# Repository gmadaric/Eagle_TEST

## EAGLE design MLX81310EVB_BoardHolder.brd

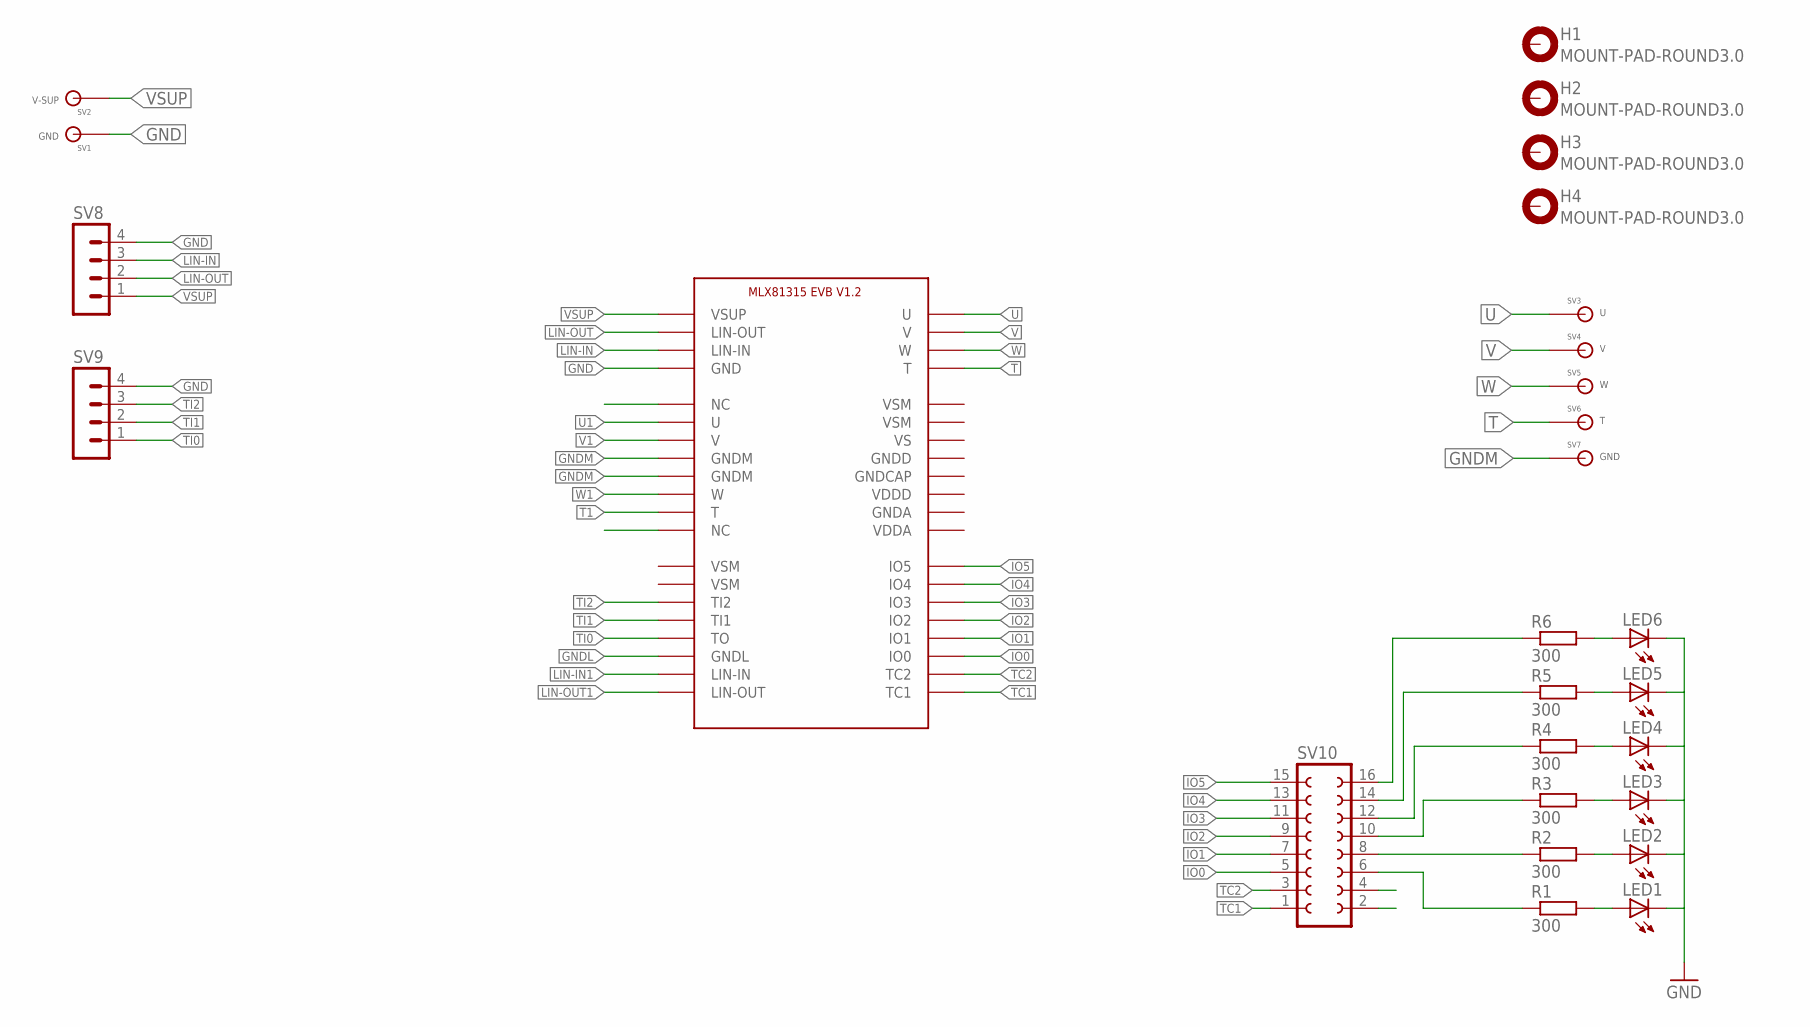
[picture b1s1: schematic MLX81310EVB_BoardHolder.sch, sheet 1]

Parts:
B1: MLX91315_EVB; MLX81315EVB
H1, H2, H3, H4: MOUNT-PAD-ROUND3.0; 3,0-PAD
LED1, LED2, LED3, LED4, LED5, LED6: LEDCHIPLED_0805; CHIPLED_0805; DIGI-KEY 160-1218-1-ND
R1, R2, R3, R4, R5, R6: 300; M0805; DIGI-KEY RR12P300DCT-ND
SV1, SV7: GND; BANANNA_CONNECTOR_SOLIDER_4MM
SV2: V-SUP; BANANNA_CONNECTOR_SOLIDER_4MM
SV3: U; BANANNA_CONNECTOR_SOLIDER_4MM
SV4: V; BANANNA_CONNECTOR_SOLIDER_4MM
SV5: W; BANANNA_CONNECTOR_SOLIDER_4MM
SV6: T; BANANNA_CONNECTOR_SOLIDER_4MM
SV8, SV9: MA04-1; DIGI-KEY 732-5317-ND
SV10: FE08-2; DIGI-KEY 609-3364-ND

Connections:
GND: B1.GND@1 (GND), LED1.C, LED2.C, LED3.C, LED4.C, LED5.C, LED6.C, SV1.P$1, SV8.4, SV9.4
GNDL: B1.GNDL
GNDM: B1.GNDM@1 (GNDM), B1.GNDM@2 (GNDM), SV7.P$1
IO0: B1.IO0, SV10.5
IO1: B1.IO1, SV10.7
IO2: B1.IO2, SV10.9
IO3: B1.IO3, SV10.11
IO4: B1.IO4, SV10.13
IO5: B1.IO5, SV10.15
LIN-IN: B1.LIN-IN@1 (LIN-IN), SV8.3
LIN-IN1: B1.LIN-IN@2 (LIN-IN)
LIN-OUT: B1.LIN-OUT@1 (LIN-OUT), SV8.2
LIN-OUT1: B1.LIN-OUT@2 (LIN-OUT)
unnamed: R6.1, SV10.16
unnamed: R4.1, SV10.12
unnamed: R1.1, SV10.6
unnamed: R2.1, SV10.8
unnamed: LED1.A, R1.2
unnamed: R3.1, SV10.10
unnamed: R5.1, SV10.14
unnamed: LED6.A, R6.2
unnamed: LED5.A, R5.2
unnamed: LED4.A, R4.2
unnamed: LED3.A, R3.2
unnamed: LED2.A, R2.2
T: B1.T@1 (T), SV6.P$1
T1: B1.T@2 (T)
TC1: B1.TC1, SV10.1, SV10.2
TC2: B1.TC2, SV10.3, SV10.4
TI0: B1.T0 (TO), SV9.1
TI1: B1.TI1, SV9.2
TI2: B1.TI2, SV9.3
U: B1.U@1 (U), SV3.P$1
U1: B1.U@2 (U)
V: B1.V@1 (V), SV4.P$1
V1: B1.V@2 (V)
VSUP: B1.VSUP, SV2.P$1, SV8.1
W: B1.W@1 (W), SV5.P$1
W1: B1.W@2 (W)

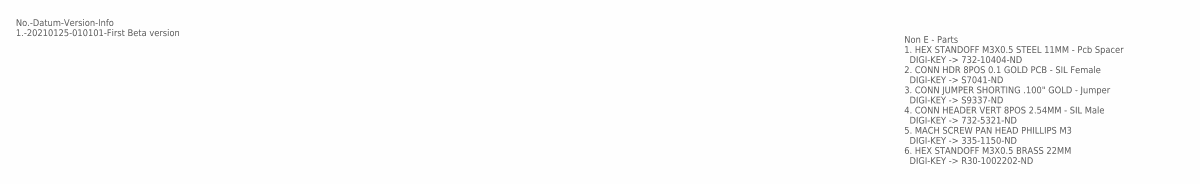
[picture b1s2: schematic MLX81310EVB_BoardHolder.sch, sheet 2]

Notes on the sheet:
No.-Datum-Version-Info 1.-20210125-010101-First Beta version
Non E - Parts 1. HEX STANDOFF M3X0.5 STEEL 11MM - Pcb Spacer DIGI-KEY -> 732-10404-ND 2. CONN HDR 8POS 0.1 GOLD PCB - SIL Female DIGI-KEY -> S7041-ND 3. CONN JUMPER SHORTING .100" GOLD - Jumper DIGI-KEY -> S9337-ND 4. CONN HEADER VERT 8POS 2.54MM - SIL Male DIGI-KEY -> 732-5321-ND 5. MACH SCREW PAN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

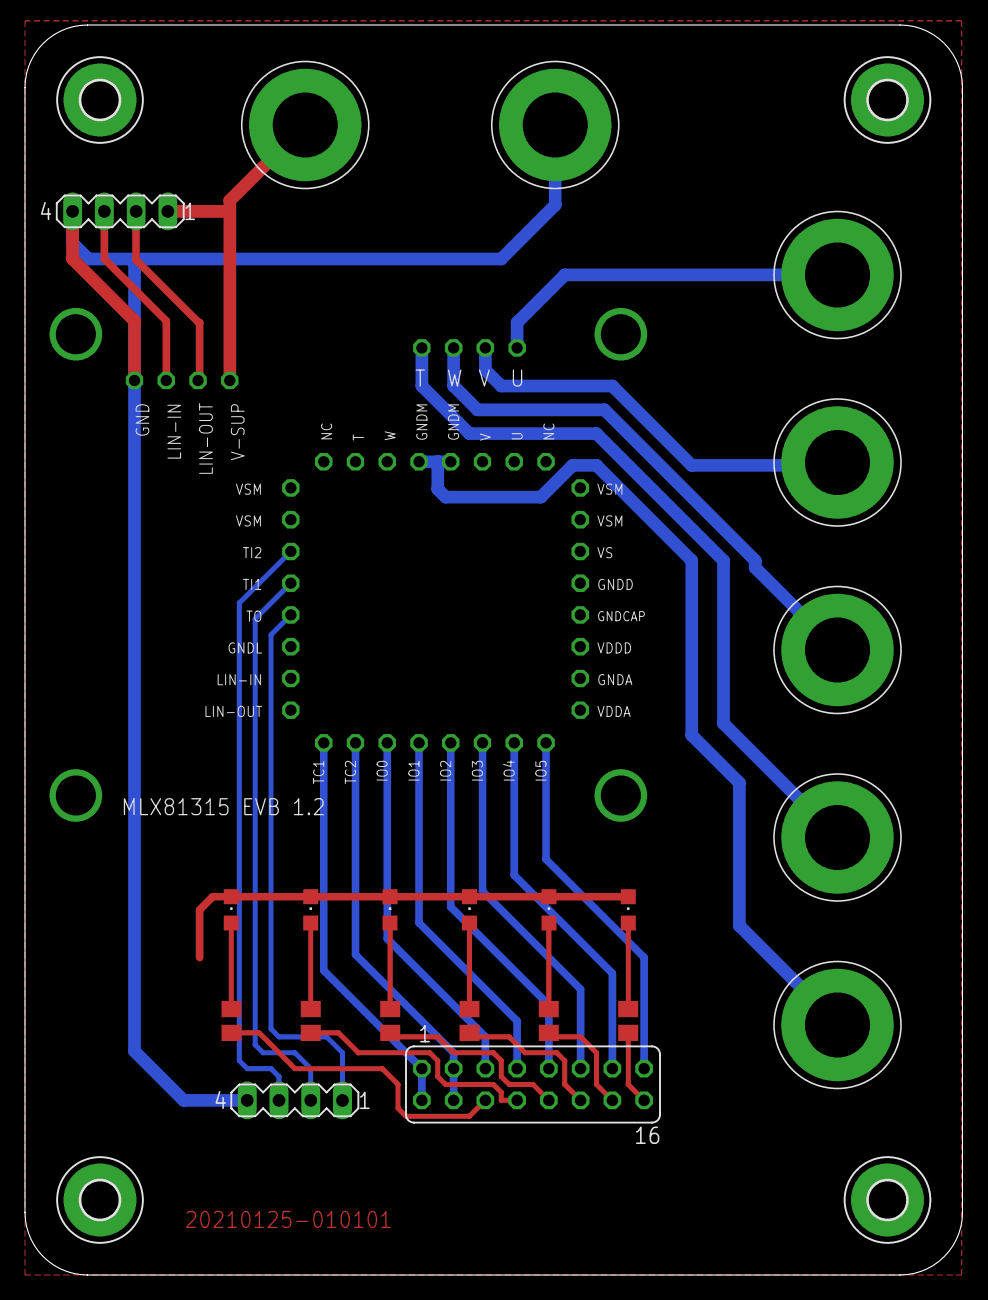
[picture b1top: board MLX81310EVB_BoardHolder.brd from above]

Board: 2 copper layers, 75.0 x 100.0 mm, 27 parts (0 on the bottom side), 32 nets.

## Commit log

2021-02-04 Label added in SCH
2021-02-04 Label 3 test
2021-02-04 Label 3 added
2021-02-04 test 4
